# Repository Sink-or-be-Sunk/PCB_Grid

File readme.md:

# Sink or be Sunk Grid PCB (Subcomponent)

This project contains the KiCAD PCB for one row of the attack of ship position boards
## Helpful Notes

### Nested Sheets

In KiCAD you can use a neat feature to split your project into multiple files. This not only helps to reduce cluter on one single diagram, it also allows for reuse of a common schematic element.

For this project specifically, the Grid.sch file can be reused for both the top (attack) grid and the bottom (ship positioning) grid.

`Hierarchical Labels` - KiCAD allows you to place a label on a nested sheet that can be viewed by the parenet sheet. Ex: you place a label on the STM32 Sheet and you can connect to it from the Main Layout schematic.

- Locate the `Hierarchical Labels` button on the right hand toolbar in kicad to place a label in a child sheet.
  - See section A4 of the STM32 Sheet
- Navigate back to the parent sheet and right click on the child sheet where you jused added the label
- Select the `import sheet pins` option
  - NOTE that you will have to do this for every new pin that you add to the child sheet, kinda repetative if you have a bunch of heirarchical labels...

`ESP32 Reference Design` - Adafruit produced a reference/dev board for the ESP32. They have great documentation on the device and are generous enough to include images of their schematic. This is a good place to start for our design. See the [Adafruit Website](https://learn.adafruit.com/adafruit-huzzah32-esp32-feather/downloads) for details.

#### Gride/Row PCB Updates

Started making some progress on our PCB layout. I'm already a little worried about space constraints. For a little more reference on the sizing: the width of the board is 22cm (2.5cm of extra clearance + 8in(20.32cm) = 22.82cm, rounded to 22cm to be on the safe side) and the length/height of the board is 2cm (0.787in). I was thinking to align one edge of each PCB with the edge of the grid - moreover, keep the 2.5cm extra all to one side for the resistor array, mux, connectors, etc.

The resistor array is pretty large, and I think we may have some issues trying to fit it on the board without running into a grid square. The same goes for the mux and the connectors we have chosen. On the brightside, if we make the board 2cm tall then that gives roughly 0.5cm of spacing between the boards. That's a good chunk of room. I'm trying to account for the wire connections, but could we thread the wires underneath the board? It will be on standoffs anyway.

Some things to consider:
- Is the resistor array worth it? Individual resistors = more solder time, resistor array = space constraints 
- Realistically, do we need a gap between rows? If so, how much? 

Looking forward, I think this PCB will be much simpler to layout, but will take a LOT of focus and attention to detail. The spacing is the most important part of this board. We will need to double, triple check this before purchasing.

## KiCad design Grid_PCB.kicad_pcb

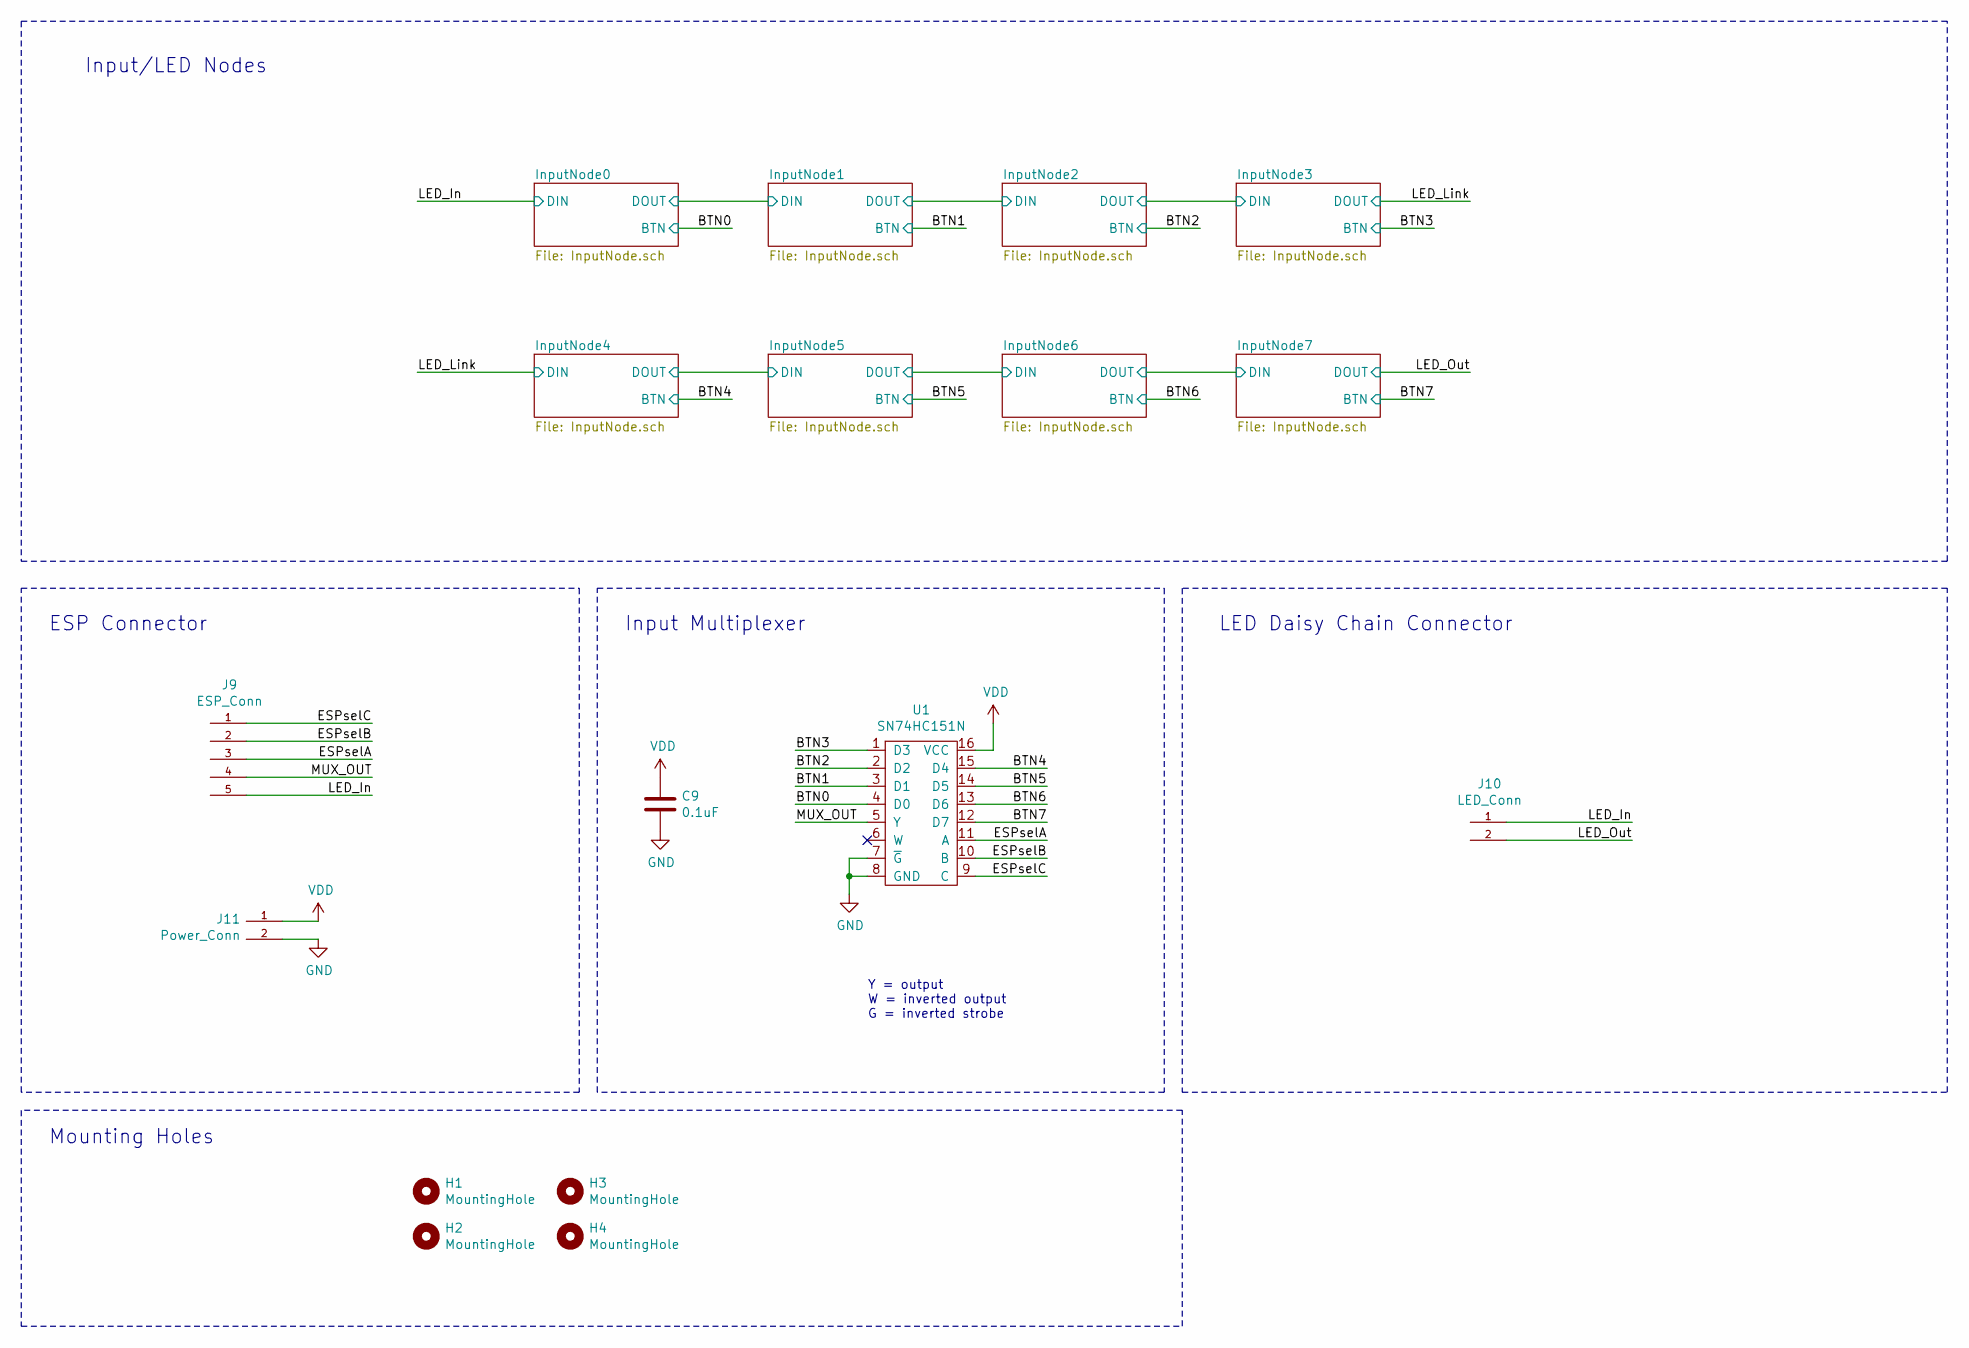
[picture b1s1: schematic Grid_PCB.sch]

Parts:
C9: 0.1uF; C_0805_2012Metric_Pad1.18x1.45mm_HandSolder
H1, H2, H3, H4: MountingHole; MountingHole_3.2mm_M3
J9: ESP_Conn; TE_640456-5
J10: LED_Conn; TE_640456-2
J11: Power_Conn; TE_640456-2
U1: SN74HC151N; DIP-16_W10.16mm

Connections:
/BTN1: U1.3 (D1); also elsewhere on the board
/BTN2: U1.2 (D2); also elsewhere on the board
/BTN3: U1.1 (D3); also elsewhere on the board
/BTN4: U1.15 (D4); also elsewhere on the board
/BTN6: U1.13 (D6); also elsewhere on the board
/BTN7: U1.12 (D7); also elsewhere on the board
/ESPselA: J9.3, U1.11 (A)
/ESPselB: J9.2, U1.10 (B)
/ESPselC: J9.1, U1.9 (C)
/LED_In: J9.5, J10.1; also elsewhere on the board
/LED_Out: J10.2; also elsewhere on the board
/MUX_OUT: J9.4, U1.5 (Y)
GND: C9.2, J11.2, U1.7 (~G), U1.8 (GND); also elsewhere on the board
VDD: C9.1, J11.1, U1.16 (VCC); also elsewhere on the board

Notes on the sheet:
Y = output W = inverted output G = inverted strobe
Input/LED Nodes
ESP Connector
Input Multiplexer
LED Daisy Chain Connector
Mounting Holes

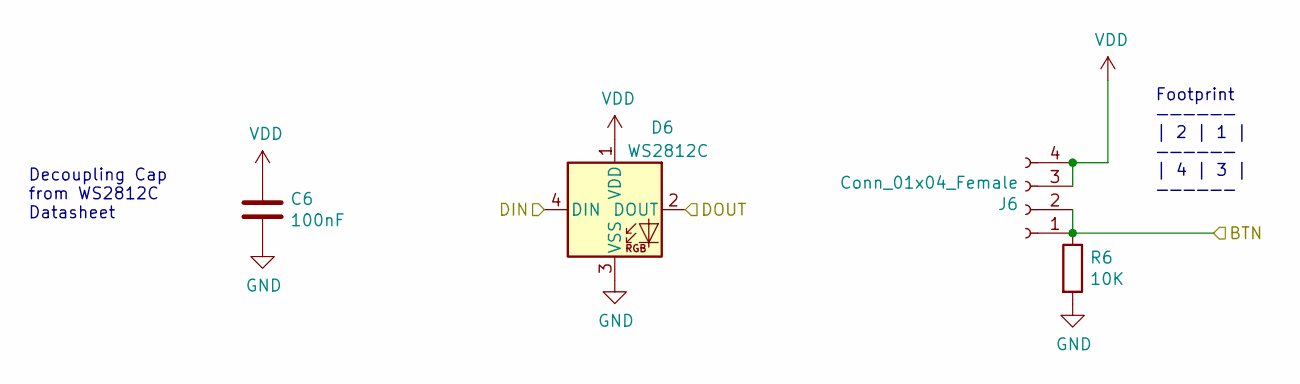
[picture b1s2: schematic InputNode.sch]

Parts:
C1: 100nF; C_0805_2012Metric_Pad1.15x1.40mm_HandSolder
D1: WS2812C; LED_WS2812B_PLCC4_5.0x5.0mm_P3.2mm
J6: Conn_01x04_Female; PinSocket_2x02_P2.54mm_Vertical
R1: 10K; R_0805_2012Metric_Pad1.20x1.40mm_HandSolder

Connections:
/InputNode1/DIN: D1.2 (DOUT); also elsewhere on the board
/LED_In: D1.4 (DIN); also elsewhere on the board
GND: C1.2, D1.3 (VSS), R1.2; also elsewhere on the board
VDD: C1.1, D1.1 (VDD), J6.3, J6.4; also elsewhere on the board

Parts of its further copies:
C2, C3, C4, C5, C6, C7, C8: 100nF; C_0805_2012Metric_Pad1.15x1.40mm_HandSolder
D2, D3, D4, D5, D6, D7, D8: WS2812C; LED_WS2812B_PLCC4_5.0x5.0mm_P3.2mm
J1, J2, J3, J4, J5, J7, J8: Conn_01x04_Female; PinSocket_2x02_P2.54mm_Vertical
R2, R3, R4, R5, R6, R7, R8: 10K; R_0805_2012Metric_Pad1.20x1.40mm_HandSolder

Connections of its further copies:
/BTN1: J2.1, J2.2, R2.1; also elsewhere on the board
/BTN2: J3.1, J3.2, R3.1; also elsewhere on the board
/BTN3: J4.1, J4.2, R4.1; also elsewhere on the board
/BTN4: J5.1, J5.2, R5.1; also elsewhere on the board
/BTN6: J7.1, J7.2, R7.1; also elsewhere on the board
/BTN7: J8.1, J8.2, R8.1; also elsewhere on the board
/InputNode1/DIN: D2.4 (DIN); also elsewhere on the board
/InputNode2/DIN: D2.2 (DOUT), D3.4 (DIN)
/InputNode3/DIN: D3.2 (DOUT), D4.4 (DIN)
/InputNode5/DIN: D5.2 (DOUT), D6.4 (DIN)
/InputNode6/DIN: D6.2 (DOUT), D7.4 (DIN)
/InputNode7/DIN: D7.2 (DOUT), D8.4 (DIN)
/LED_Link: D4.2 (DOUT), D5.4 (DIN)
/LED_Out: D8.2 (DOUT); also elsewhere on the board
GND: C2.2, C3.2, C4.2, C5.2, C6.2, C7.2, C8.2, D2.3 (VSS), D3.3 (VSS), D4.3 (VSS), D5.3 (VSS), D6.3 (VSS), D7.3 (VSS), D8.3 (VSS), R2.2, R3.2, R4.2, R5.2, R6.2, R7.2, R8.2; also elsewhere on the board
VDD: C2.1, C3.1, C4.1, C5.1, C6.1, C7.1, C8.1, D2.1 (VDD), D3.1 (VDD), D4.1 (VDD), D5.1 (VDD), D6.1 (VDD), D7.1 (VDD), D8.1 (VDD), J1.3, J1.4, J2.3, J2.4, J3.3, J3.4, J4.3, J4.4, J5.3, J5.4, J7.3, J7.4, J8.3, J8.4; also elsewhere on the board

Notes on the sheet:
Decoupling Cap from WS2812C Datasheet
Footprint —————— | 2 | 1 | —————— | 4 | 3 | ——————

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
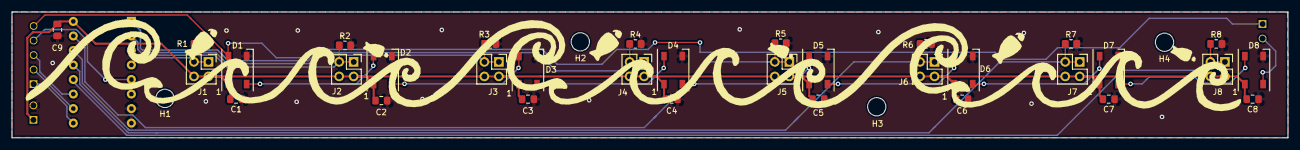
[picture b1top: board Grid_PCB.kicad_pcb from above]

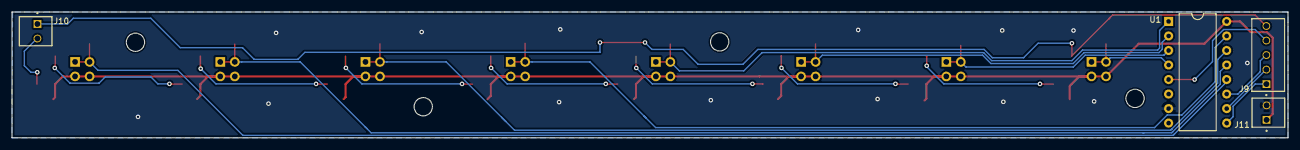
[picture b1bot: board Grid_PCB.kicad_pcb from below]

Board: 2 copper layers, 223.2 x 22.0 mm, 41 parts (4 on the bottom side), 23 nets.

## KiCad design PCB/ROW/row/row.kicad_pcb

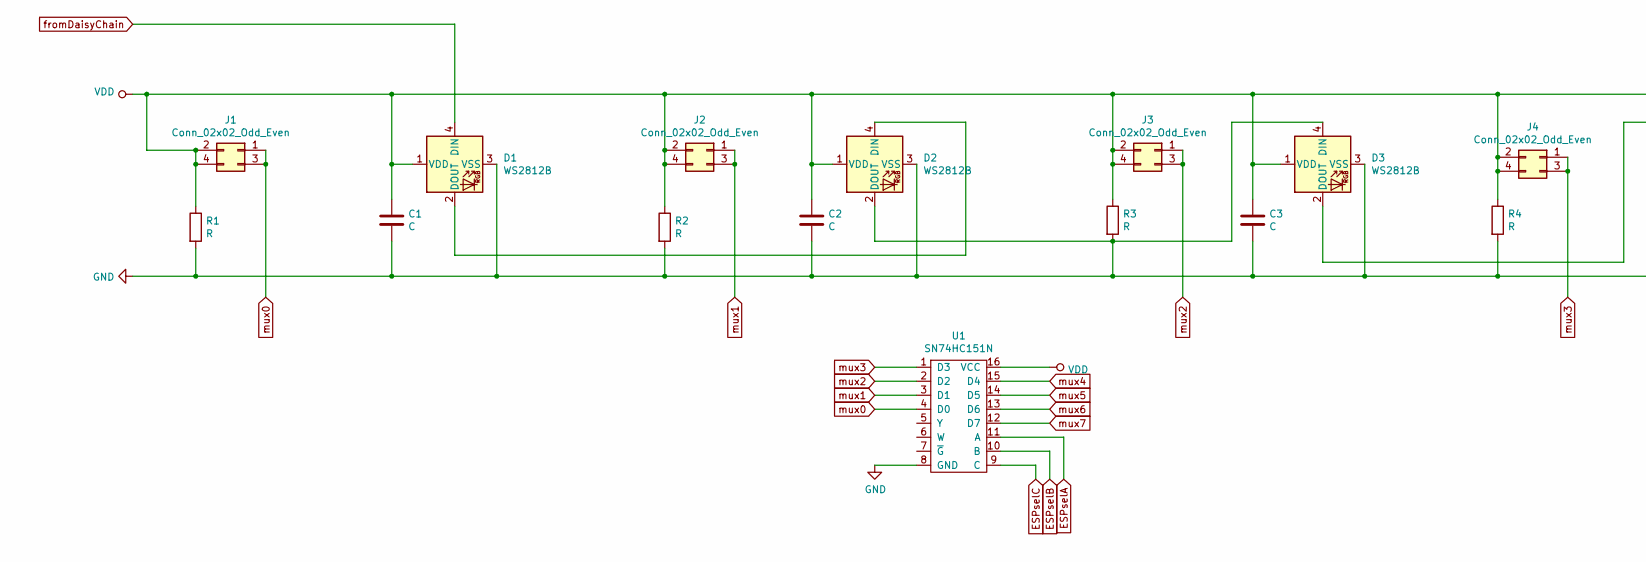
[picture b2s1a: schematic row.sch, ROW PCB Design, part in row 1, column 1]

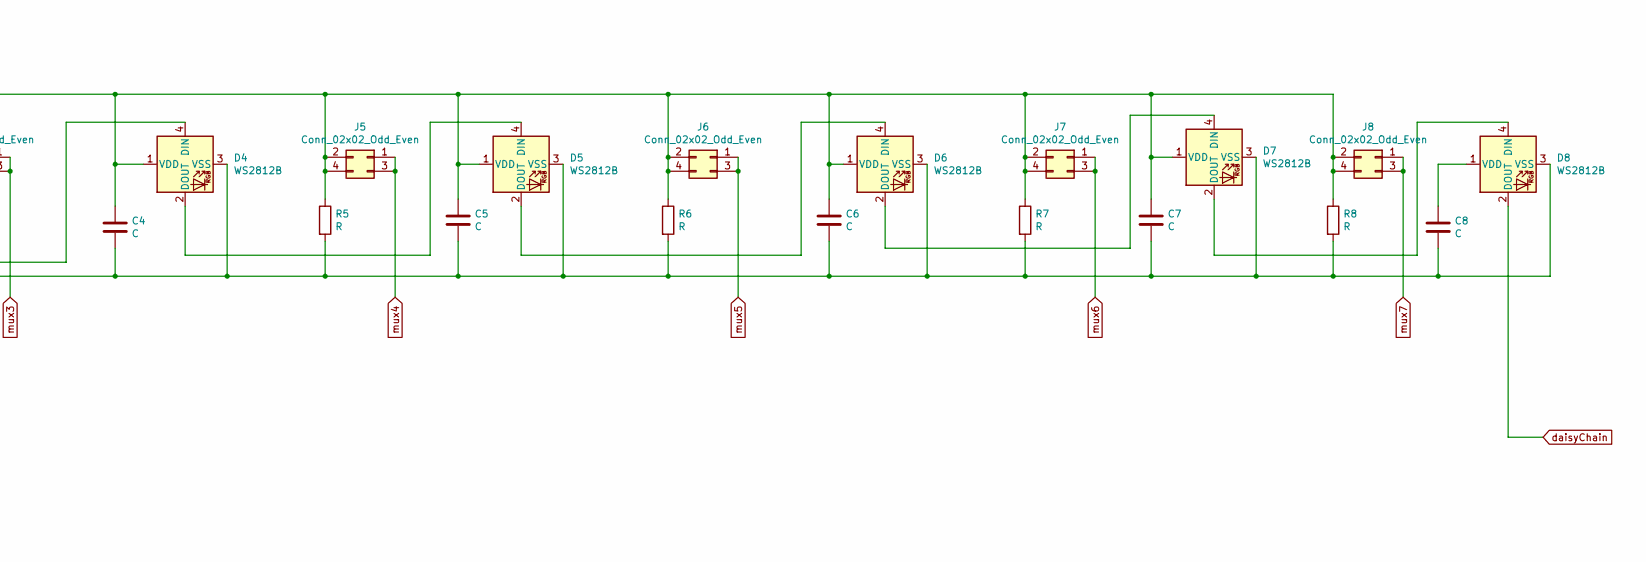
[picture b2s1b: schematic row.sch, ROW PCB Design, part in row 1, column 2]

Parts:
C1, C2, C3, C4, C5, C6, C7, C8: C; C_0805_2012Metric_Pad1.15x1.40mm_HandSolder
D1, D2, D3, D4, D5, D6, D7, D8: WS2812B; LED_WS2812B_PLCC4_5.0x5.0mm_P3.2mm
J1, J2, J3, J4, J5, J6, J7, J8: Conn_02x02_Odd_Even; PinSocket_2x02_P2.54mm_Vertical
R1, R2, R3, R4, R5, R6, R7, R8: R; R_0805_2012Metric_Pad1.15x1.40mm_HandSolder
U1: SN74HC151N; SN74HC151N-PDIP

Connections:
ESPselA: U1.11 (A)
ESPselB: U1.10 (B)
ESPselC: U1.9 (C)
GND: C1.2, C2.2, C3.2, C4.2, C5.2, C6.2, C7.2, C8.2, D1.3 (VSS), D2.2 (DOUT), D2.3 (VSS), D3.3 (VSS), D3.4 (DIN), D4.3 (VSS), D5.3 (VSS), D6.3 (VSS), D7.3 (VSS), D8.3 (VSS), R1.2, R2.2, R3.2, R4.2, R5.2, R6.2, R7.2, R8.2, U1.8 (GND)
unnamed: C8.1, D8.1 (VDD)
unnamed: D1.2 (DOUT), D2.4 (DIN)
unnamed: D3.2 (DOUT), D4.4 (DIN)
unnamed: D4.2 (DOUT), D5.4 (DIN)
unnamed: D5.2 (DOUT), D6.4 (DIN)
unnamed: D6.2 (DOUT), D7.4 (DIN)
unnamed: D7.2 (DOUT), D8.4 (DIN)
VDD: C1.1, C2.1, C3.1, C4.1, C5.1, C6.1, C7.1, D1.1 (VDD), D2.1 (VDD), D3.1 (VDD), D4.1 (VDD), D5.1 (VDD), D6.1 (VDD), D7.1 (VDD), J1.2, J1.4, J2.2, J2.4, J3.2, J3.4, J4.2, J4.4, J5.2, J5.4, J6.2, J6.4, J7.2, J7.4, J8.2, J8.4, R1.1, R2.1, R3.1, R4.1, R5.1, R6.1, R7.1, R8.1, U1.16 (VCC)
daisyChain: D8.2 (DOUT)
fromDaisyChain: D1.4 (DIN)
mux0: J1.1, J1.3, U1.4 (D0)
mux1: J2.1, J2.3, U1.3 (D1)
mux2: J3.1, J3.3, U1.2 (D2)
mux3: J4.1, J4.3, U1.1 (D3)
mux4: J5.1, J5.3, U1.15 (D4)
mux5: J6.1, J6.3, U1.14 (D5)
mux6: J7.1, J7.3, U1.13 (D6)
mux7: J8.1, J8.3, U1.12 (D7)

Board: 2 copper layers, 33 parts (0 on the bottom side), 17 nets, no tracks yet.

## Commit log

2021-09-28 First Draft of Row/Grid PCB
2021-09-28 transered nested project into root and moved docs into docs/ folder
2021-10-01 temp
2021-10-01 updated for homepage
2021-10-04 added resistor network and updated mnt hole footprint
2021-10-06 PCB layout updates
2021-10-06 continued progress
2021-10-06 finished first pass at routing
2021-10-07 updated with todo for routing around screws
2021-10-09 trace update
2021-10-11 flipped components to back side
2021-10-12 rotated the mux
2021-10-12 minor silkscreen and mounting hole fix
2021-10-12 fixed added cap for mux and fixed drc errors
2021-10-13 finsihed sch and pcb
2021-10-13 minor fix to mux strobe (enable) pin
2021-10-14 updated conns and mounting holes
2021-10-14 updated conns, moved mounting holes
2021-10-19 updated jst footprint/library and updated routing on sel signals
2021-10-19 updated hole footprint
2021-10-20 first attempt at waves
2021-10-21 wave pattern attempt
2021-10-21 wave 2
2021-10-21 wave 2 light
2021-10-21 wave 3
2021-10-21 wave 4
2021-10-21 wave 4 skinny
2021-10-21 wave fish
2021-10-21 wave fish middle
2021-10-21 wave fish thin, like this one the best
2021-10-21 pruned footprint library
